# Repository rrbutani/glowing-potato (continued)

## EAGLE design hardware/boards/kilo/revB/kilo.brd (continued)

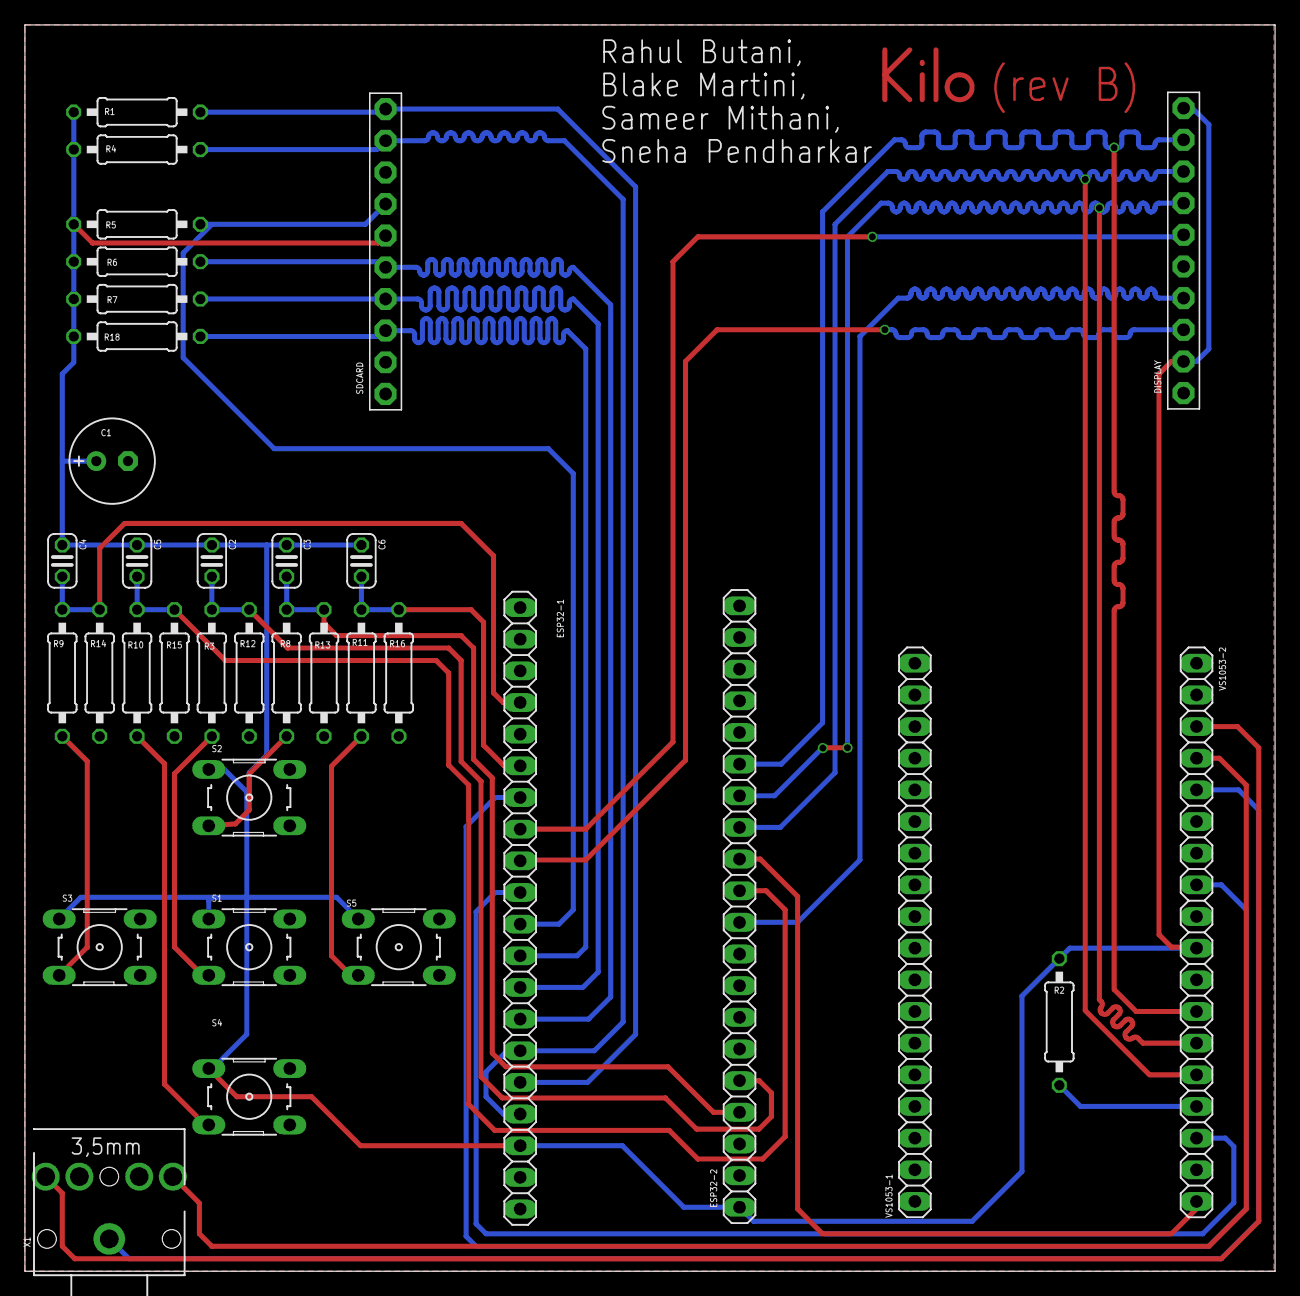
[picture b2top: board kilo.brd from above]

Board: 2 copper layers, 100.3 x 100.0 mm, 35 parts (0 on the bottom side), 31 nets.

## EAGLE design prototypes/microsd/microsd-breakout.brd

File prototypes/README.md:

## Prototypes:

- Clickwheel (ATQ + wheel on FR-4)
- SD Card (microSD Card pin breakout)
- Buttons (push buttons + diodes on a breadboard; ADC + DIN)
- Display (other ILI9314 w/FPC connector on FR-4)
- VS1053 (Adafruit breakout on a breadboard)

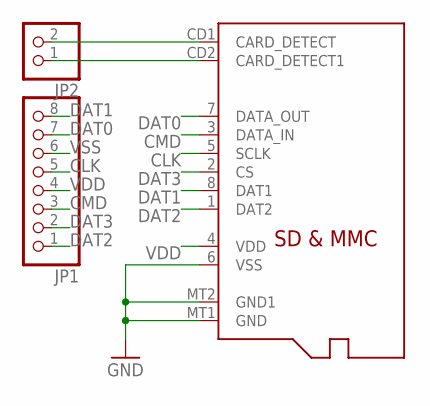
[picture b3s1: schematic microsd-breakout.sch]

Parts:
JP1: PINHD-1X8/90; 1X08/90
JP2: PINHD-1X2/90; 1X02/90
U$1: MICROSD

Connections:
CLK: JP1.5, U$1.5 (SCLK)
CMD: JP1.3, U$1.3 (DATA_IN)
DAT0: JP1.7, U$1.7 (DATA_OUT)
DAT1: JP1.8, U$1.8 (DAT1)
DAT2: JP1.1, U$1.1 (DAT2)
DAT3: JP1.2, U$1.2 (CS)
unnamed: JP2.1, U$1.CD2 (CARD_DETECT1)
unnamed: JP2.2, U$1.CD1 (CARD_DETECT)
VDD: JP1.4, U$1.4 (VDD)
VSS: JP1.6, U$1.6 (VSS), U$1.MT1 (GND), U$1.MT2 (GND1)

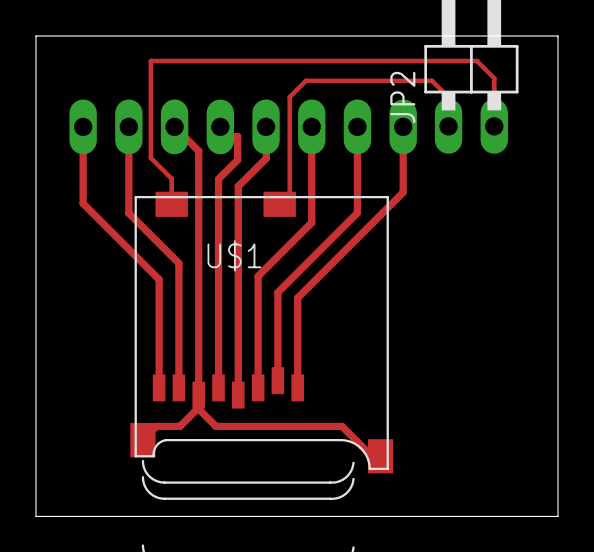
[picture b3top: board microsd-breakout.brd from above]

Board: 2 copper layers, 29.0 x 26.7 mm, 3 parts (1 on the bottom side), 10 nets.

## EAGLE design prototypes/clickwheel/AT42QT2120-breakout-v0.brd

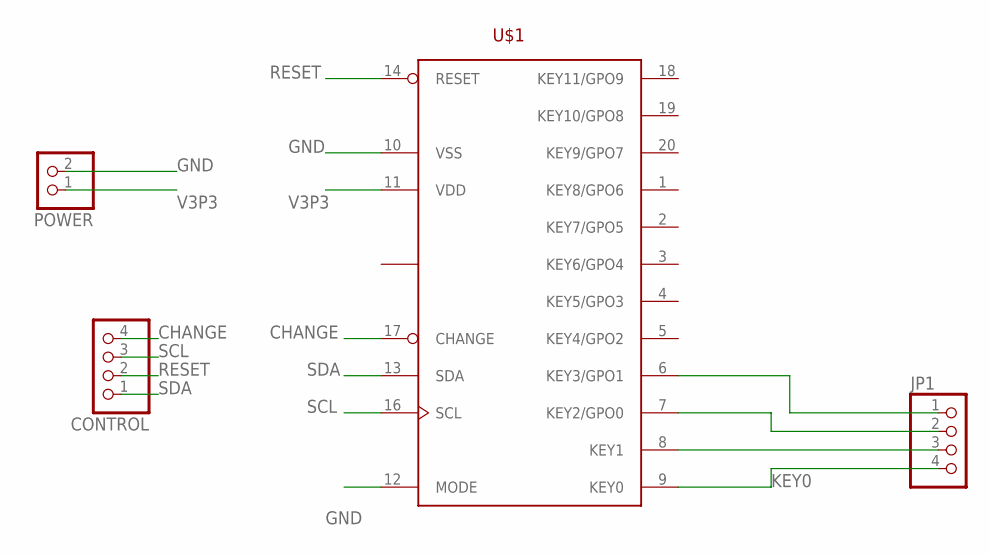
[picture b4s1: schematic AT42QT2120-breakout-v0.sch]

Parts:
CONTROL: PINHD-1X4/90; 1X04/90
JP1: PINHD-1X4/90; 1X04/90
POWER: PINHD-1X2/90; 1X02/90
U$1: COMMS-AT42QT2120SU; SO20W

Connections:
CHANGE: CONTROL.4, U$1.17 (CHANGE)
GND: POWER.2, U$1.10 (VSS), U$1.12 (MODE)
KEY0: JP1.4, U$1.9 (KEY0)
unnamed: JP1.1, U$1.6 (KEY3/GPO1)
unnamed: JP1.3, U$1.8 (KEY1)
unnamed: JP1.2, U$1.7 (KEY2/GPO0)
RESET: CONTROL.2, U$1.14 (RESET)
SCL: CONTROL.3, U$1.16 (SCL)
SDA: CONTROL.1, U$1.13 (SDA)
V3P3: POWER.1, U$1.11 (VDD)

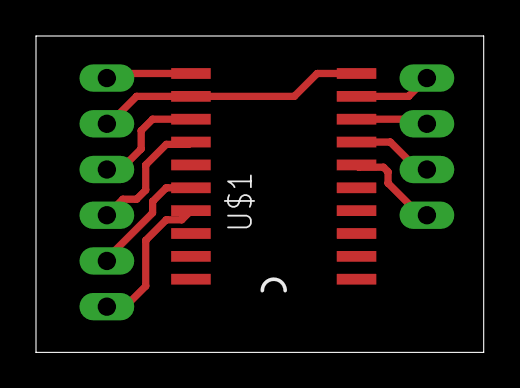
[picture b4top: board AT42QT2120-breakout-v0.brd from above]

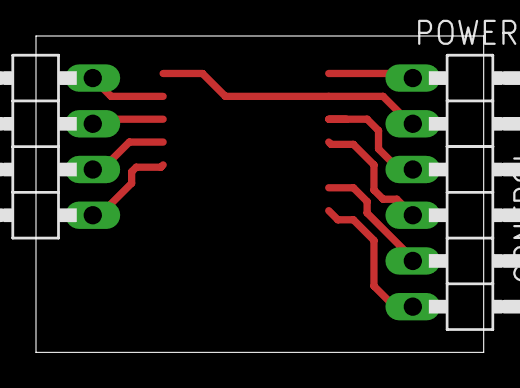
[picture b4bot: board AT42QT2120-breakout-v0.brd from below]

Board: 2 copper layers, 24.9 x 17.6 mm, 4 parts (3 on the bottom side), 10 nets.

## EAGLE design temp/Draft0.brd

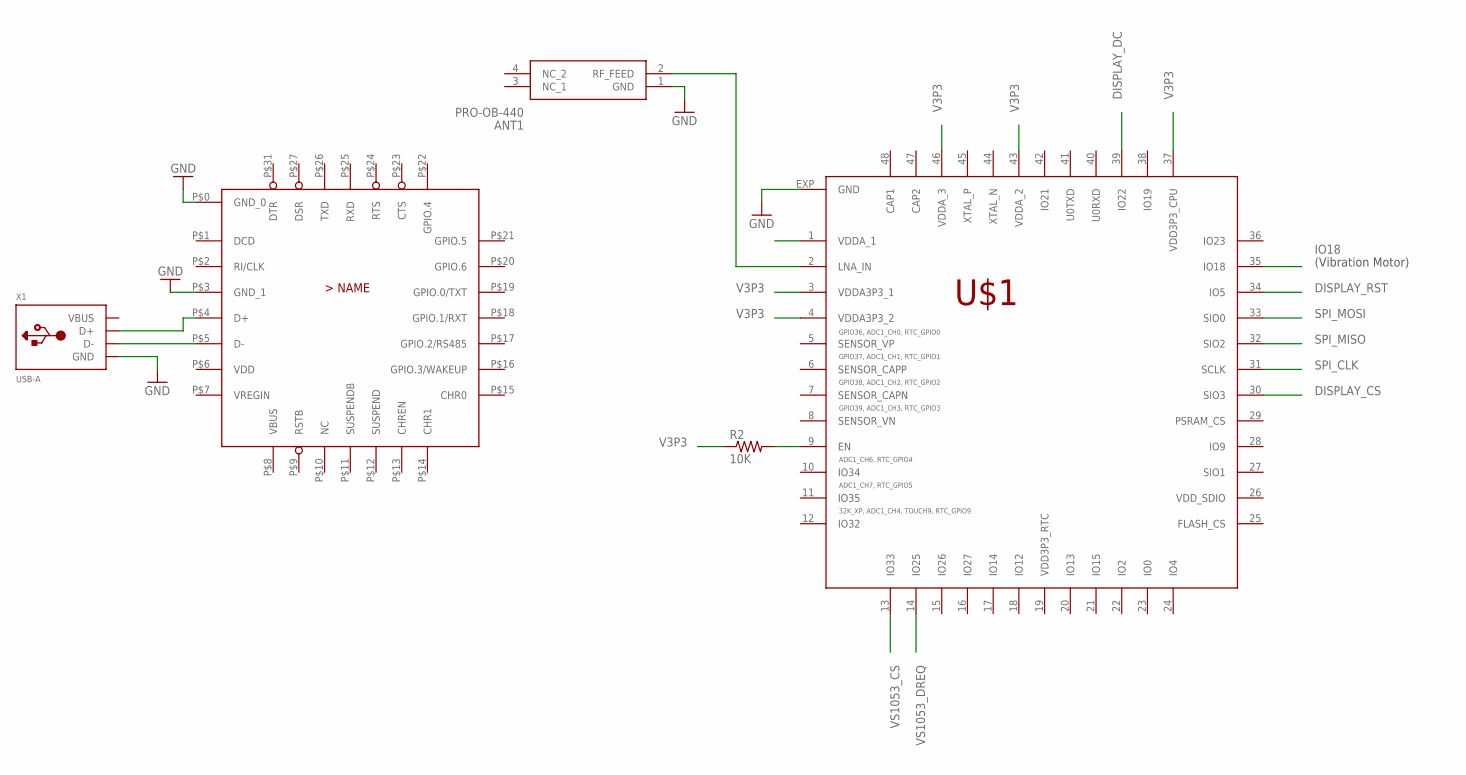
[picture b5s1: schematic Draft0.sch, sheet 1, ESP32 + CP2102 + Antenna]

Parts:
ANT1: PRO-OB-440; PRO-OB-440_1
R2: 10K; M1206
U$1: ESP32-PICO-D4; QFN48
U$4: CP2102N-A02-GQFN28; QFN28
X1: USB-A; MOLEX_480371000

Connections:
DISPLAY_CS: U$1.30 (SIO3); also elsewhere on the board
DISPLAY_DC: U$1.39 (IO22); also elsewhere on the board
DISPLAY_RST: U$1.34 (IO5); also elsewhere on the board
GND: ANT1.1 (GND), U$1.EXP (GND), U$4.P$0 (GND_0), U$4.P$3 (GND_1), X1.4 (GND); also elsewhere on the board
IO18: U$1.35 (IO18); also elsewhere on the board
unnamed: R2.2, U$1.9 (EN)
unnamed: ANT1.2 (RF_FEED), U$1.2 (LNA_IN)
unnamed: U$4.P$4 (D+), X1.3 (D+)
unnamed: U$4.P$5 (D-), X1.2 (D-)
SPI_CLK: U$1.31 (SCLK); also elsewhere on the board
SPI_MISO: U$1.32 (SIO2); also elsewhere on the board
SPI_MOSI: U$1.33 (SIO0); also elsewhere on the board
V3P3: R2.1, U$1.3 (VDDA3P3_1), U$1.4 (VDDA3P3_2), U$1.37 (VDD3P3_CPU), U$1.43 (VDDA_2), U$1.46 (VDDA_3); also elsewhere on the board
VBUS: X1.1 (VBUS)
VDD: U$4.P$6 (VDD)
VDD3P3_RTC: U$1.19 (VDD3P3_RTC)
VDD_SDIO: U$1.26 (VDD_SDIO)
VREGIN: U$4.P$7 (VREGIN)
VS1053_CS: U$1.13 (IO33); also elsewhere on the board
VS1053_DREQ: U$1.14 (IO25); also elsewhere on the board

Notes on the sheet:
(Vibration Motor)

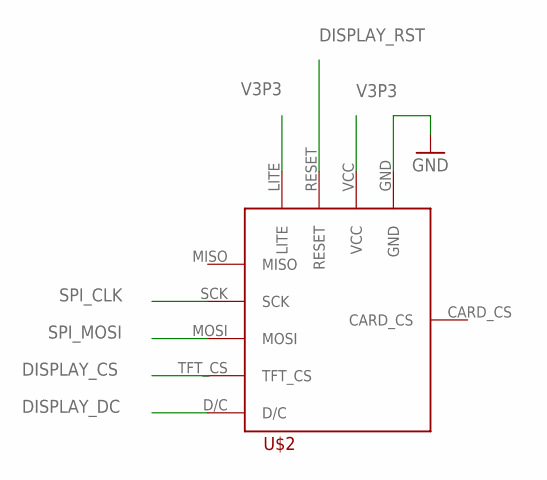
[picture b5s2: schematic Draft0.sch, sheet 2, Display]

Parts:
U$2: ADAFRUITST7735R_18

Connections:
DISPLAY_CS: U$2.TFT_CS; also elsewhere on the board
DISPLAY_DC: U$2.D/C; also elsewhere on the board
DISPLAY_RST: U$2.RESET; also elsewhere on the board
GND: U$2.GND; also elsewhere on the board
SPI_CLK: U$2.SCK; also elsewhere on the board
SPI_MOSI: U$2.MOSI; also elsewhere on the board
V3P3: U$2.LITE, U$2.VCC; also elsewhere on the board

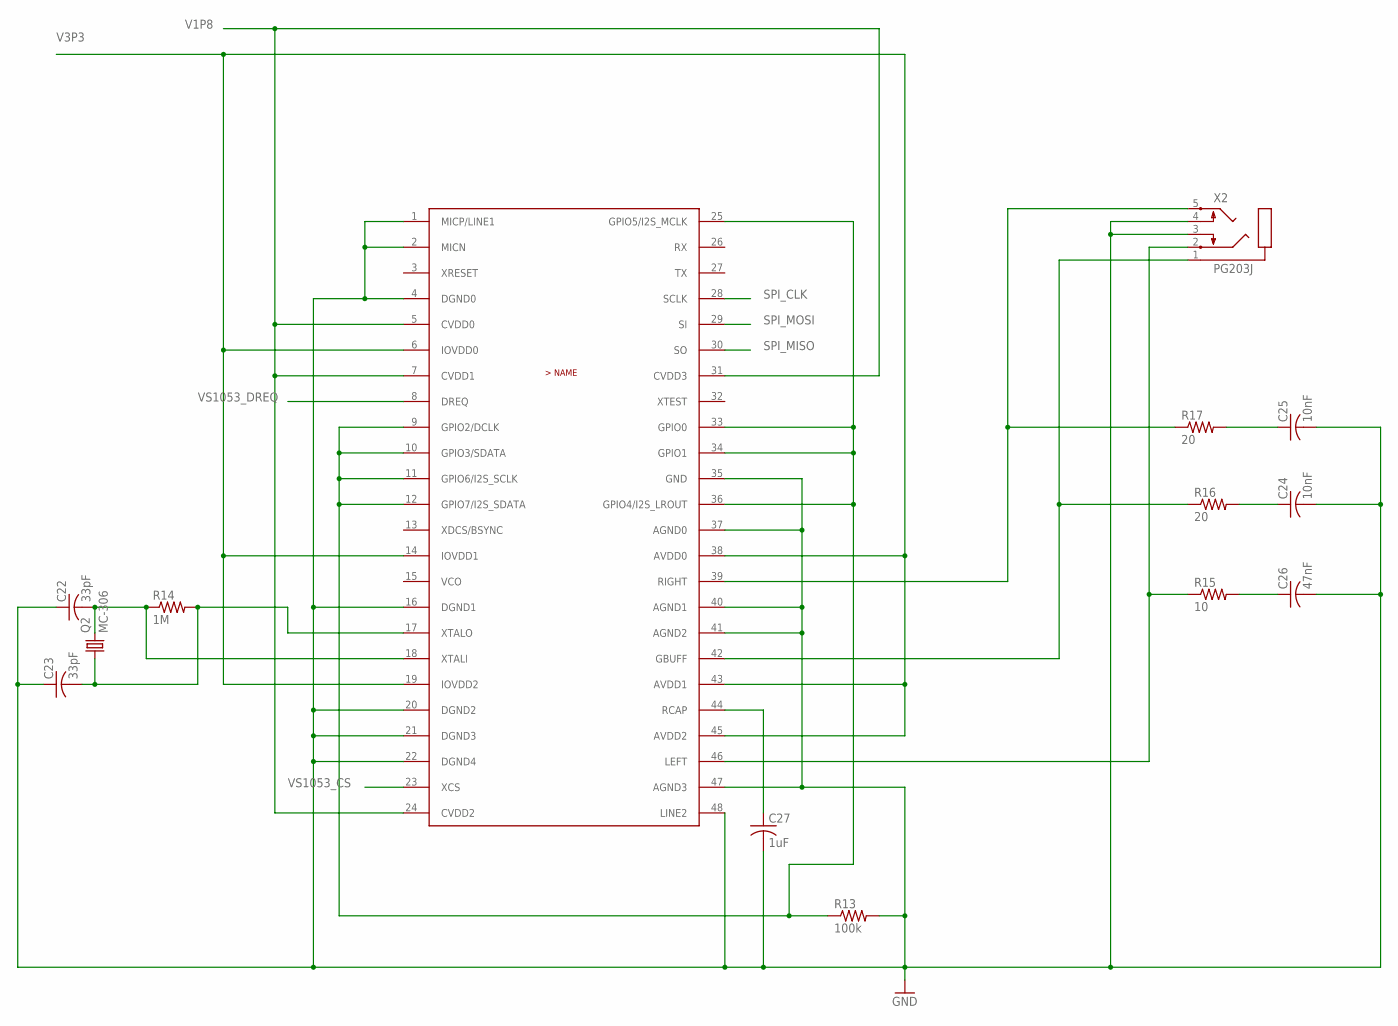
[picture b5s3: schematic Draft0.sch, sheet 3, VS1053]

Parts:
C22, C23: 33pF; C0402
C24, C25: 10nF; C0201
C26: 47nF; C0201
C27: 1uF; C0201
Q2: MC-306
R13: 100k; 1812X7R
R14: 1M; 1812X7R
R15: 10; R01005
R16, R17: 20; R01005
U$7: VS1053; LQFP48
X2: PG203J

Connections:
GND: C22.1, C23.1, C24.2, C25.2, C26.2, C27.2, R13.2, U$7.1 (MICP/LINE1), U$7.2 (MICN), U$7.4 (DGND0), U$7.16 (DGND1), U$7.20 (DGND2), U$7.21 (DGND3), U$7.22 (DGND4), U$7.35 (GND), U$7.37 (AGND0), U$7.40 (AGND1), U$7.41 (AGND2), U$7.47 (AGND3), U$7.48 (LINE2), X2.3, X2.4; also elsewhere on the board
unnamed: C23.2, Q2.1, R14.2, U$7.17 (XTALO)
unnamed: R13.1, U$7.9 (GPIO2/DCLK), U$7.10 (GPIO3/SDATA), U$7.11 (GPIO6/I2S_SCLK), U$7.12 (GPIO7/I2S_SDATA), U$7.25 (GPIO5/I2S_MCLK), U$7.33 (GPIO0), U$7.34 (GPIO1), U$7.36 (GPIO4/I2S_LROUT)
unnamed: C22.2, Q2.4 (2), R14.1, U$7.18 (XTALI)
unnamed: R15.1, U$7.46 (LEFT), X2.2
unnamed: R16.1, U$7.42 (GBUFF), X2.1
unnamed: R17.1, U$7.39 (RIGHT), X2.5
unnamed: C26.1, R15.2
unnamed: C24.1, R16.2
unnamed: C25.1, R17.2
unnamed: C27.1, U$7.44 (RCAP)
SPI_CLK: U$7.28 (SCLK); also elsewhere on the board
SPI_MISO: U$7.30 (SO); also elsewhere on the board
SPI_MOSI: U$7.29 (SI); also elsewhere on the board
V1P8: U$7.5 (CVDD0), U$7.7 (CVDD1), U$7.24 (CVDD2), U$7.31 (CVDD3); also elsewhere on the board
V3P3: U$7.6 (IOVDD0), U$7.14 (IOVDD1), U$7.19 (IOVDD2), U$7.38 (AVDD0), U$7.43 (AVDD1), U$7.45 (AVDD2); also elsewhere on the board
VS1053_CS: U$7.23 (XCS); also elsewhere on the board
VS1053_DREQ: U$7.8 (DREQ); also elsewhere on the board

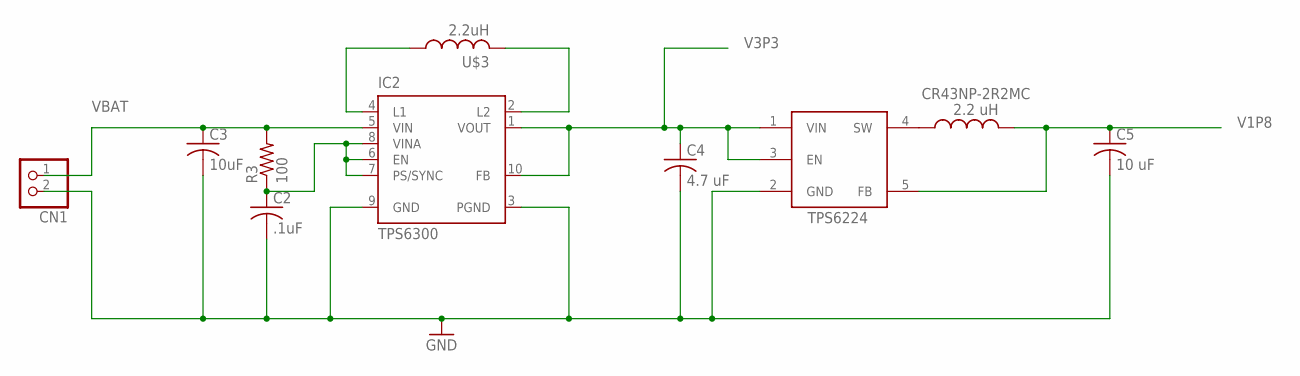
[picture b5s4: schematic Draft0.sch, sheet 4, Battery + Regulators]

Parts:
C2: .1uF; C0603
C3: 10uF; C0603
C4: 4.7 uF; C0805
C5: 10 uF; C1210
CN1: JST_2PIN-SMT-RA; JST-PH-2-SMT-RA
IC2: TPS6300; DRC-S-PVSON-N10
R3: 100; R01005
TPS6224: TPS62240; TSP62240
U$3: 2.2uH; INDUCTOR
U$5: CR43NP-2R2MC; INDUCTOR

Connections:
GND: C2.2, C3.2, C4.2, C5.2, CN1.2 (1), IC2.3 (PGND), IC2.9 (GND), TPS6224.2 (GND); also elsewhere on the board
unnamed: C2.1, IC2.6 (EN), IC2.7 (PS/SYNC), IC2.8 (VINA), R3.1
unnamed: IC2.2 (L2), U$3.P$2 (2)
unnamed: IC2.4 (L1), U$3.P$1 (1)
unnamed: TPS6224.4 (SW), U$5.P$1 (1)
V1P8: C5.1, TPS6224.5 (FB), U$5.P$2 (2); also elsewhere on the board
V3P3: C4.1, IC2.1 (VOUT), IC2.10 (FB), TPS6224.1 (VIN), TPS6224.3 (EN); also elsewhere on the board
VBAT: C3.1, CN1.1 (2), IC2.5 (VIN), R3.2; also elsewhere on the board

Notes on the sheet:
TPS6224

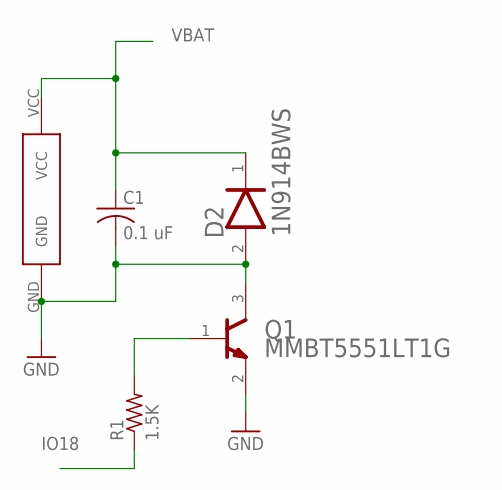
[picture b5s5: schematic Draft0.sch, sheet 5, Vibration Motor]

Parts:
C1: 0.1 uF; C025-024X044
D2: ON_SEMI_1N914BWSON_SEMI_1N914BWS_0_0; ON_SEMI_1N914BWS_0
MOT1: MINI-MOTOR
Q1: ON_SEMI_MMBT5551LT1GON_SEMI_MMBT5551LT1G_0_0; ON_SEMI_MMBT5551LT1G_0
R1: 1.5K; R0603

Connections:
GND: C1.2, D2.2 (ANODE), MOT1.GND, Q1.2 (EMITTER), Q1.3 (COLLECTOR); also elsewhere on the board
IO18: R1.1; also elsewhere on the board
unnamed: Q1.1 (BASE), R1.2
VBAT: C1.1, D2.1 (CATHODE), MOT1.VCC; also elsewhere on the board

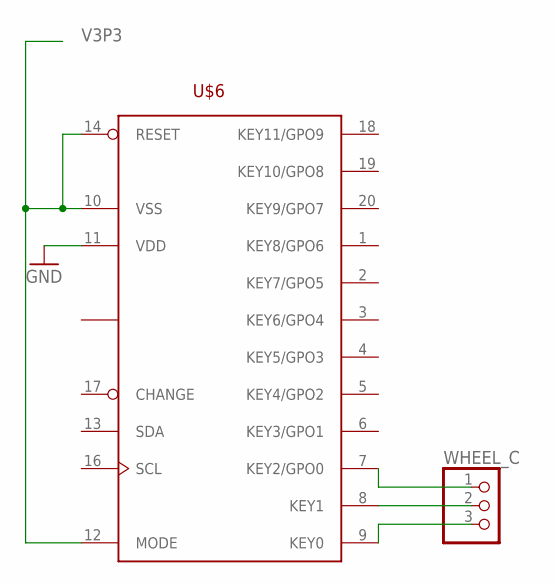
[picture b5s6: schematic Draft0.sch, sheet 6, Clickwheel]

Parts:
U$6: COMMS-AT42QT2120XU; TSSOP20
WHEEL_C: PINHD-1X3/90; 1X03/90

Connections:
GND: U$6.11 (VDD); also elsewhere on the board
unnamed: U$6.9 (KEY0), WHEEL_C.3
unnamed: U$6.8 (KEY1), WHEEL_C.2
unnamed: U$6.7 (KEY2/GPO0), WHEEL_C.1
V3P3: U$6.10 (VSS), U$6.12 (MODE), U$6.14 (RESET); also elsewhere on the board

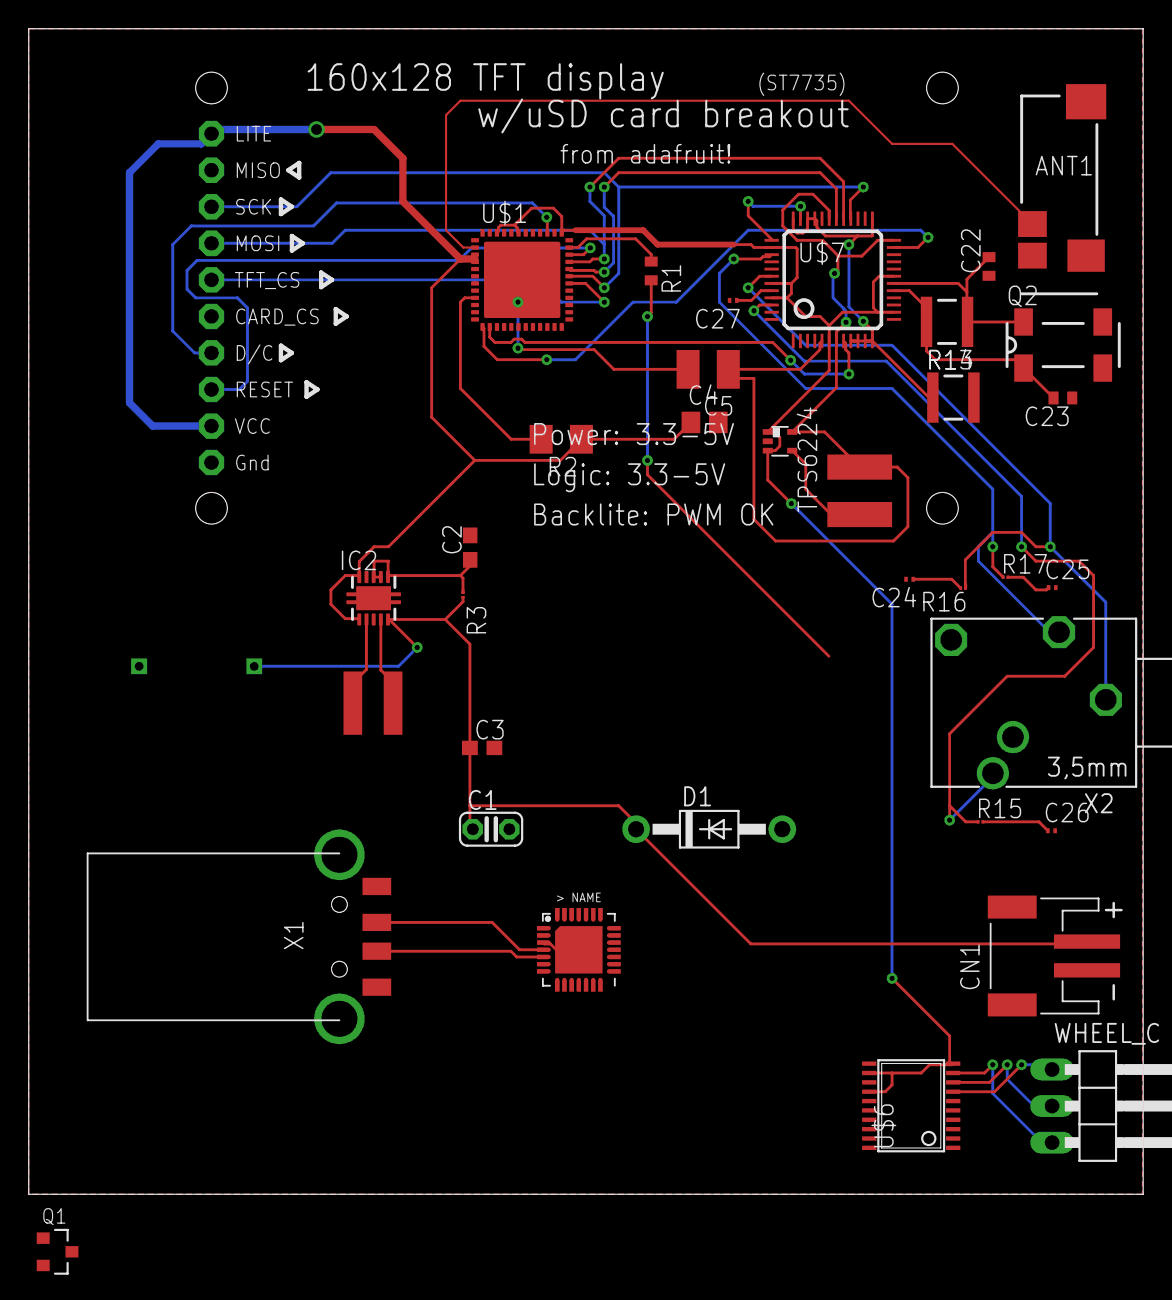
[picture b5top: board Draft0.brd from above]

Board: 2 copper layers, 77.5 x 81.0 mm, 37 parts (1 on the bottom side), 35 nets.

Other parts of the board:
D1: 1N4004; DO41-10

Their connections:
GND: D1.A; also elsewhere on the board
VBAT: D1.C; also elsewhere on the board

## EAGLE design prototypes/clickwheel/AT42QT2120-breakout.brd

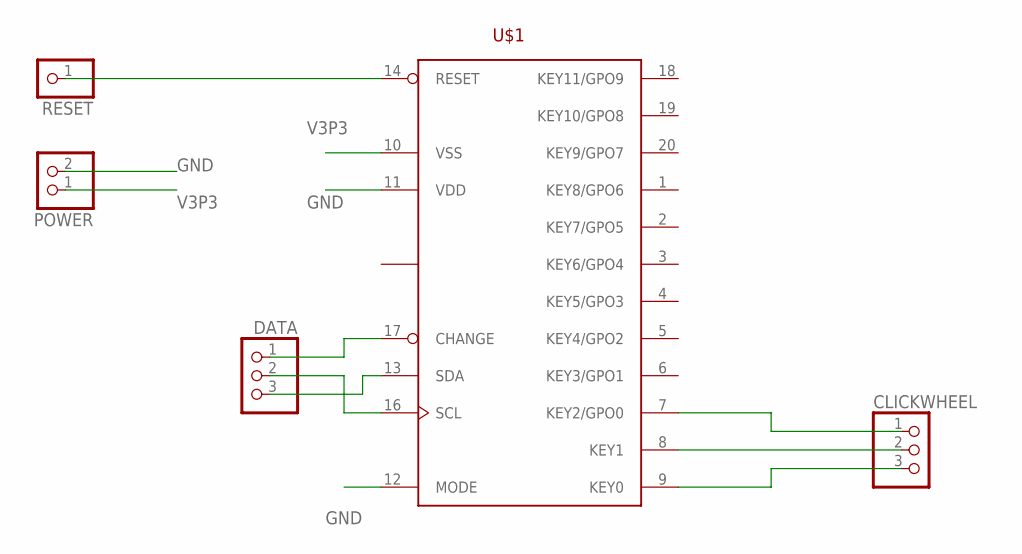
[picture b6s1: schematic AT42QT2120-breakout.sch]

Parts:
CLICKWHEEL: PINHD-1X3/90; 1X03/90
DATA: PINHD-1X3/90; 1X03/90
POWER: PINHD-1X2/90; 1X02/90
RESET: PINHD-1X1; 1X01
U$1: COMMS-AT42QT2120SU; SO20W

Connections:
GND: POWER.2, U$1.11 (VDD), U$1.12 (MODE)
unnamed: RESET.1, U$1.14 (RESET)
unnamed: DATA.1, U$1.17 (CHANGE)
unnamed: DATA.2, U$1.16 (SCL)
unnamed: CLICKWHEEL.3, U$1.9 (KEY0)
unnamed: CLICKWHEEL.2, U$1.8 (KEY1)
unnamed: CLICKWHEEL.1, U$1.7 (KEY2/GPO0)
unnamed: DATA.3, U$1.13 (SDA)
V3P3: POWER.1, U$1.10 (VSS)

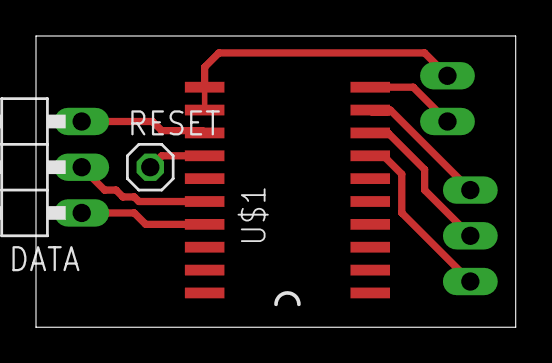
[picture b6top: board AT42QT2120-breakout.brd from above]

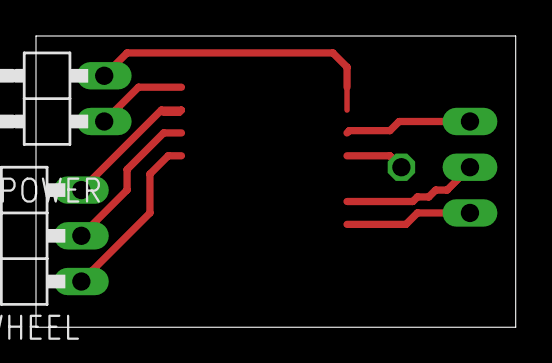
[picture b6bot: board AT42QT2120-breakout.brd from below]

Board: 2 copper layers, 26.6 x 16.2 mm, 5 parts (2 on the bottom side), 9 nets.

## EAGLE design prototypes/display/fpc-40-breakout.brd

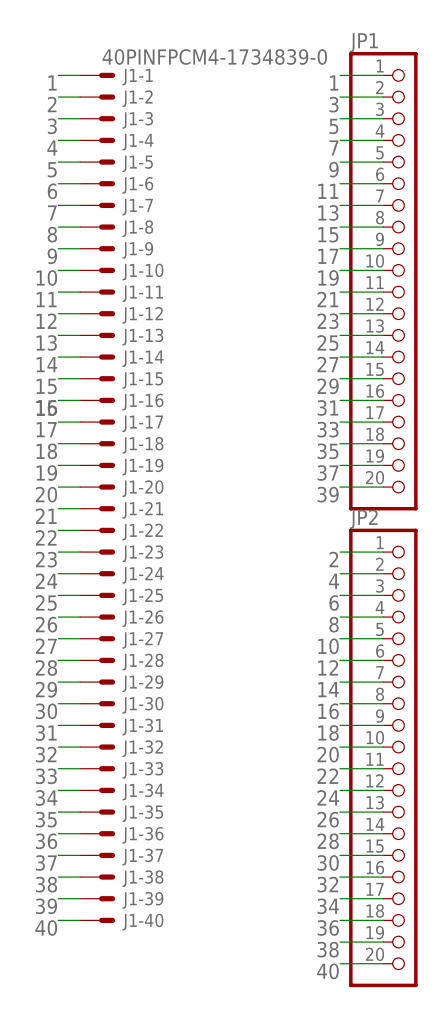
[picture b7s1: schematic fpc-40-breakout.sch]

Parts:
J1: 40PINFPCM4-1734839-0; 4-1734839-0
JP1, JP2: PINHD-1X20/90; 1X20/90

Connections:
1: J1.1 (MSV), JP1.1
2: J1.2 (MS), JP2.1
3: J1.3 (MS), JP1.2
4: J1.4 (MS), JP2.2
5: J1.5 (MS), JP1.3
6: J1.6 (MS), JP2.3
7: J1.7 (MS), JP1.4
8: J1.8 (MS), JP2.4
9: J1.9 (MS), JP1.5
10: J1.10 (MS), JP2.5
11: J1.11 (MS), JP1.6
12: J1.12 (MS), JP2.6
13: J1.13 (MS), JP1.7
14: J1.14 (MS), JP2.7
15: J1.15 (MS), JP1.8
16: J1.16 (MS), JP2.8
17: J1.17 (MS), JP1.9
18: J1.18 (MS), JP2.9
19: J1.19 (MS), JP1.10
20: J1.20 (MS), JP2.10
21: J1.21 (MS), JP1.11
22: J1.22 (MS), JP2.11
23: J1.23 (MS), JP1.12
24: J1.24 (MS), JP2.12
25: J1.25 (MS), JP1.13
26: J1.26 (MS), JP2.13
27: J1.27 (MS), JP1.14
28: J1.28 (MS), JP2.14
29: J1.29 (MS), JP1.15
30: J1.30 (MS), JP2.15
31: J1.31 (MS), JP1.16
32: J1.32 (MS), JP2.16
33: J1.33 (MS), JP1.17
34: J1.34 (MS), JP2.17
35: J1.35 (MS), JP1.18
36: J1.36 (MS), JP2.18
37: J1.37 (MS), JP1.19
38: J1.38 (MS), JP2.19
39: J1.39 (MS), JP1.20
40: J1.40 (MS), JP2.20

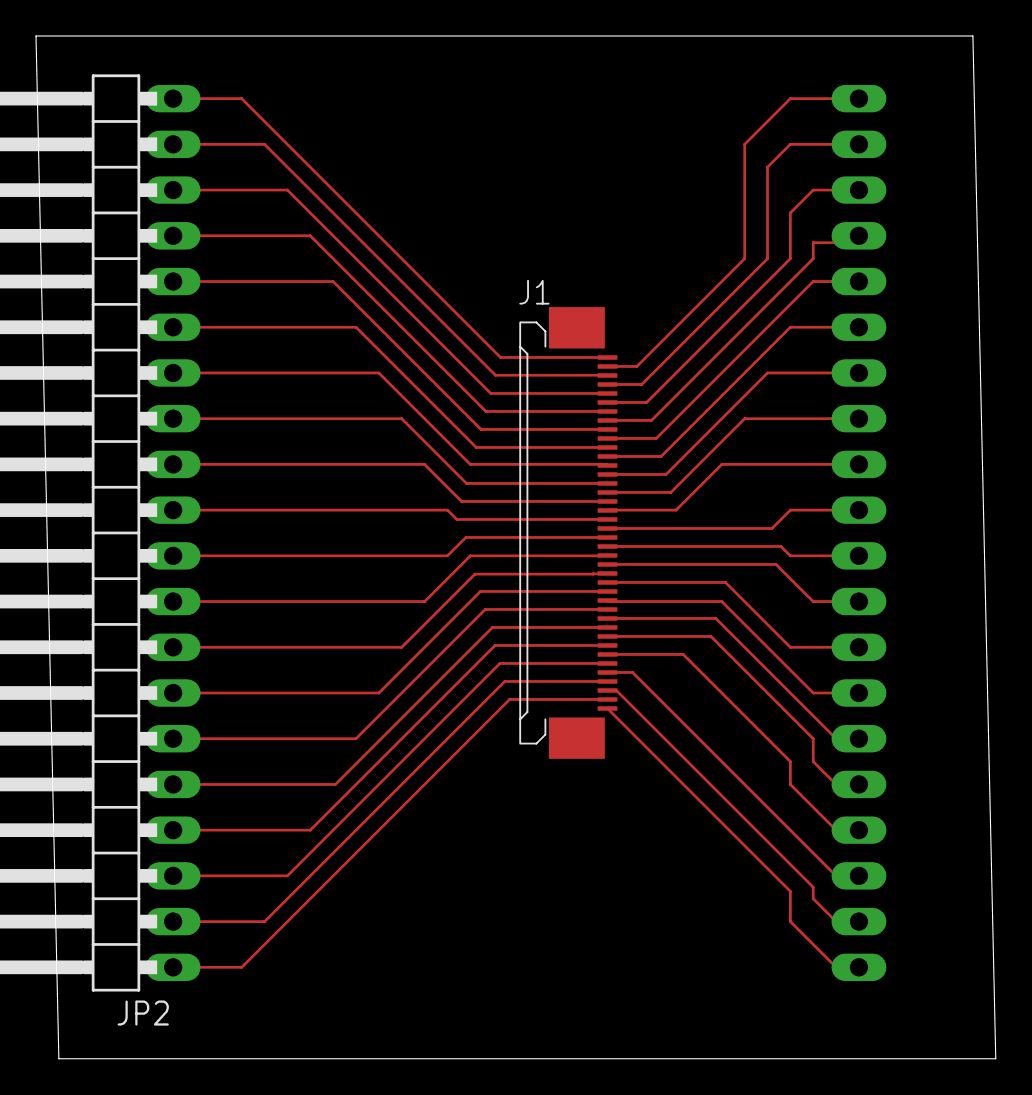
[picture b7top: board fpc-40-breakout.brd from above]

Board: 2 copper layers, 53.3 x 56.8 mm, 3 parts (1 on the bottom side), 40 nets.

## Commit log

2019-03-15 AT42QT2120 eagle library: still need to add the standalone device
2019-03-15 update AT42AT2120 library
2019-03-15 breakout!
2019-03-18 steal a reasonable gitignore
2019-03-18 checkpoint: wheel script
2019-03-18 ignore everything but markdown files in docs/
2019-03-18 checkpoint
2019-03-19 checkpoint: an unsuccessful yak shave in progress
2019-03-21 how many channels?
    you can pick!
2019-03-21 minor fixes
2019-03-22 fix channel numbering
2019-03-23 more yakshaving: now with vectors
2019-03-24 checkpoint: changes from the plane
2019-03-25 hw: first pass at an esp32 part
2019-03-25 Added VS1053 library
2019-03-28 lab07: a draft
2019-03-28 added vs1053 pcb considerations
2019-03-29 full vlsi product library added
2019-03-29 Power regulator added
2019-03-29 miscellanious parts for power
2019-03-29 CP2102N: hopefully correct
2019-03-29 Proant 440 Antenna: borrowed
2019-03-29 added voltage regulater data sheets
2019-03-29 a wheel prototype!
2019-03-29 misc library changes from the night
2019-03-29 it almost works! still needs some hand-holding but we're getting there
2019-03-29 lab07: pre-checkout? not proud but it's what we sbumitted
2019-03-30 still has tiny airwires, but good enough for now
2019-04-01 VS1053 schematic
    I left the UART and board lines as open wires
2019-04-04 updated motor
2019-04-04 jst 3 pin XH SMT library
2019-04-04 added header for motor
2019-04-04 TRRS footprint and symbol
2019-04-04 added some libraries
2019-04-04 minor tweaks
2019-04-04 housekeeping
2019-04-05 updated screen
2019-04-05 screen fixes
2019-04-05 update esp32 library
2019-04-05 add some additional parts
2019-04-05 start our CAD collection
2019-04-05 i am bad at electricity
2019-04-05 our very flat switch
2019-04-05 add ESD protection diode
2019-04-05 checkpoint: USB
2019-04-05 update LED part
2019-04-05 checkpoint: LED, battery voltage circuit, charge IC, half of the CP2102N
2019-04-05 checkpoint: power on and off circuit
2019-04-05 misc VS1053 fixes + fix/wire ATQ
2019-04-05 add labels so my head stops throbbing
2019-04-05 inline + tip switch (bad) + ??
2019-04-05 ECS122.8
2019-04-05 antenna and its very specific friends
2019-04-05 added testpads
2019-04-05 just the pinmap left!!
2019-04-05 schematic: done!?
2019-04-05 minor fixes: this is an adjustable 1.8V regulator..
2019-04-07 prototype plan
2019-04-08 update ATQ breakouts
2019-04-08 display fpc breakout
2019-04-08 move and rename the wheel pattern script
2019-04-09 update .gitignore for our new programs
2019-04-12 notes
2019-04-13 update ATQ prototype board files
2019-04-13 get rid of temp
2019-04-13 switch licenses to something we'd actually want when we eventually make this public (MIT)
2019-04-13 some stubs for later
2019-04-13 we're actually going to _not_ use a library for the wheel; just a regular part
2019-04-13 add our names
2019-04-14 Power on/off changes + misc fixes
    Corrected the power on/off circuit (connected the top of the switch to the right net) and bumped up the resistor value so that it'll take ~6 seconds of the power button being held down to power off.
    The circuit should now match Figure 5 from [this](http://www.mosaic-industries.com/embedded-systems/microcontroller-projects/electronic-circuits/push-button-switch-turn-on/latching-toggle-power-switc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
    This fixes #1.
    Additionally, libraries used in the V0 files should match the rearranged folders.
2019-04-14 Add voltage comparator eagle library
    For #4
2019-04-14 Add UVLO protection (using an APX809S-31SA)
    Closes #4
2019-04-14 Update power on/off notes
    Closes #8
2019-04-14 Swap center buttons for 100Q (lower actuation force) variants
2019-04-14 add missing esp32 capacitor values
2019-04-14 Add charge detect back in, using up all our pins
    Closes #11
2019-04-15 checkpoint: swapped resistors for the esp32/cp2102N/usb port, routed the usb port, and swapped the power source for the CP2102N (runs off the 3.3V regulator now; no sense in the device appearing on c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
2019-04-15 clean up some cruft
2019-04-15 board checkpoint
2019-04-15 (unverified) design rules for JLCPCB
2019-04-19 added pull ups to SD card
2019-04-20 Swap resistors for the microSD Card
    10k pull-ups on everything appears to work (50k does not even though some of the guides say otherwise).
    Only 1-line MMC mode works so far, but there's still stuff to try.
2019-04-20 Add an experimental card detect input to the ADC button circuit
    If this is problematic we can just remove/not populate the resistor for CARD_DETECT (R54). Just adding an input to the ADC and not the full diode + digital input line too because we can just poll the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
2019-04-21 Bridge IO0 and IO2 so that we can flash the board and use an SD Card
    From the message on sheet 1:
    IO2 is a strapping pin that allows the esp32 to enter download mode (iirc) - it's required to be pulled low when flashing the esp. Unforuntately, we have to use IO2 for the one usable SD/MMC interfac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
    IO0 is also a strapping pin: it's connected to RTS on the CP2102N and is pulled low when we're flashing the board. So, if we tie IO0 to IO2, IO2 will be pulled down while flashing. This solves our pr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
    Unforunately this means that we can't use IO0 for anything else since it remains tied to IO2 (anything we do to IO0 will affect the SD/MMC
2019-04-22 Breakout board for an Adafruit microSD Card slot
    Got 4 line MMC to work. Turns out it had nothing to do with the breakout or the pull-up resistor values or the breadboard. Instead, the wires were just too long/crappy. 🤷
    This closes #7.
2019-04-22 add some docs
2019-04-22 magnet positions: a guess
    the BOM is updated now too; gonna go with [these magnets](https://www.ebay.com/itm/1-100-Rare-Earth-Magnets-Neodymium-Round-Disk-Super-Strong-Large-Sizes-USA/122945482155), probably
    this closes #14
2019-04-22 fix magnets (3mm _diameter_ - I hope)
2019-04-22 checkpoint: 3.3V regulator
2019-04-22 checkpoint: charge IC
2019-04-22 checkpoint: vibration motor
2019-04-22 checkpoint: power on/off
2019-04-22 update Crystal library: don't put pin labels on the silkscreen
2019-04-22 no bikes
2019-04-23 checkpoint: ATQ, part 1
2019-04-23 checkpoint: 1.8V regulator, first pass
2019-04-23 fix "NAME" on CP2102N
2019-04-23 checkpoint: sd card?
2019-04-23 Add files via upload
    added button tester software, with threshold values
2019-04-24 backup done
2019-04-25 backup board with fixes
2019-04-30 swap VS1053 GPIO pull down resistors
2019-04-30 add backup header pin block for the VS1053
2019-04-30 VS1053 changes
    Switch back to bridging all the GPIO pins (the datasheet's sample connection diagram has it wired this way, so it'll hopefully not be an issue) and tie xRESET to V3P3 (pull-up) so that we can actuall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
    The Adafruit VS1053 breakout schematic mentions that they tie xRESET to low (pull-down) to avoid transients (clicks) in the headphone outputs (as per [this](http://www.vlsi.fi/uploads/media/vs10XXan.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
    At this point we seem
2019-05-02 changes to backup
2019-05-02 display prototype
2019-05-02 most routing done
2019-05-02 backup closer to done
2019-05-02 board closer
2019-05-02 housekeeping + checkpoint
2019-05-02 Redo the board for kilo, revision B (aka the backup board)
    Closes #17.
    Closes #18.
    Closes #19.
    Closes #20.
    Closes #21.
    Closes #22.
2019-05-03 checkpoint: pico is trudging along
2019-05-03 checkpoint: mostly route complete (!)
2019-05-03 checkpoint: route complete (!!)
2019-05-03 checkpoint: drc, round 1
2019-05-03 checkpoint: labels
2019-05-03 checkpoint: drc, round 2
2019-05-03 checkpoint: names and such
2019-05-03 checkpoint: pico, mostly
2019-05-03 start working on the wheel board, but really this is postponed until later
2019-05-03 add the gerber for kilo revB
2019-05-05 fix a small bug in the wheel generator
2019-05-05 wheel_gen is now interactive!
2019-05-05 flip the outer/inner circles to match the polygons (eagle's grid is reversed - that's why we have to do this)
2019-05-05 wheel-gen: dump constants into generated scr file
2019-05-05 pico: checkpoint: an outdated wheel
2019-05-05 wheel_gen: whoops
2019-05-05 button_input version 1
2019-05-05 pico: DON'T PANIC
    (yes, I know - it should've been a dolphin or a mouse. gotta save something for revision B. and it's a cute fish.)
2019-05-05 pico: add some (bad) art
2019-05-05 pico: wheel board, basically complete
2019-05-05 pico: add some shiny wheel things and update pico's images
2019-05-05 pico: K -> k
2019-05-07 fixed union declaration
2019-05-07 simple-player: first pass at a project structure
2019-05-07 simple-player: structure and build system, round 2; seems to work!
2019-05-07 simple-player: add our first component!
2019-05-07 misc: add a pre-commit hook and a clang-format config
2019-05-07 simple-player: some boilerplate
2019-05-07 simple-player: inputs (untested)
2019-05-07 simple-player: a quick test for inputs
2019-05-07 simple-player: button debouncing, though messy, appears to work
    FreeRTOS seems gnarly
2019-05-07 simple-player: clean up inputs.c and add a debounce menu option
2019-05-07 simple-player: minor fixes
2019-05-07 simple-player: first pass at the display module
    this is a cleaned up version of Sameer's code; it's missing any kind of display initialization routine and is just generally untested
2019-05-07 simple-player: add some types
2019-05-07 simple-player: first stab at display initialization code
2019-05-07 simple-player: first pass at sd_card init code (it compiles _and_ runs!)
2019-05-07 simple-player: checkpoint
2019-05-07 simple-player: sd card module seems to work (we can populate the track list)
2019-05-07 simple-player: Add ID3 (3.1 only) support!
    It detects when tracks have the 3.1 tags present and then goes and swaps out the name of those tracks with what it found.
2019-05-08 simple-player: boilerplate for the VS1053 component
2019-05-08 Added VS1053 header and source file
2019-05-08 salvage
2019-05-08 it works!?!?
2019-05-08 audio up down
2019-05-09 everything sucks! make sure you don't use Adafruit fonts (or run this code)
2019-05-09 checkpoint: trash
2019-05-10 simple-player: pull in sdcard changes
2019-05-12 Changes from the day of: text, menus, volume bounds, ID3 info
